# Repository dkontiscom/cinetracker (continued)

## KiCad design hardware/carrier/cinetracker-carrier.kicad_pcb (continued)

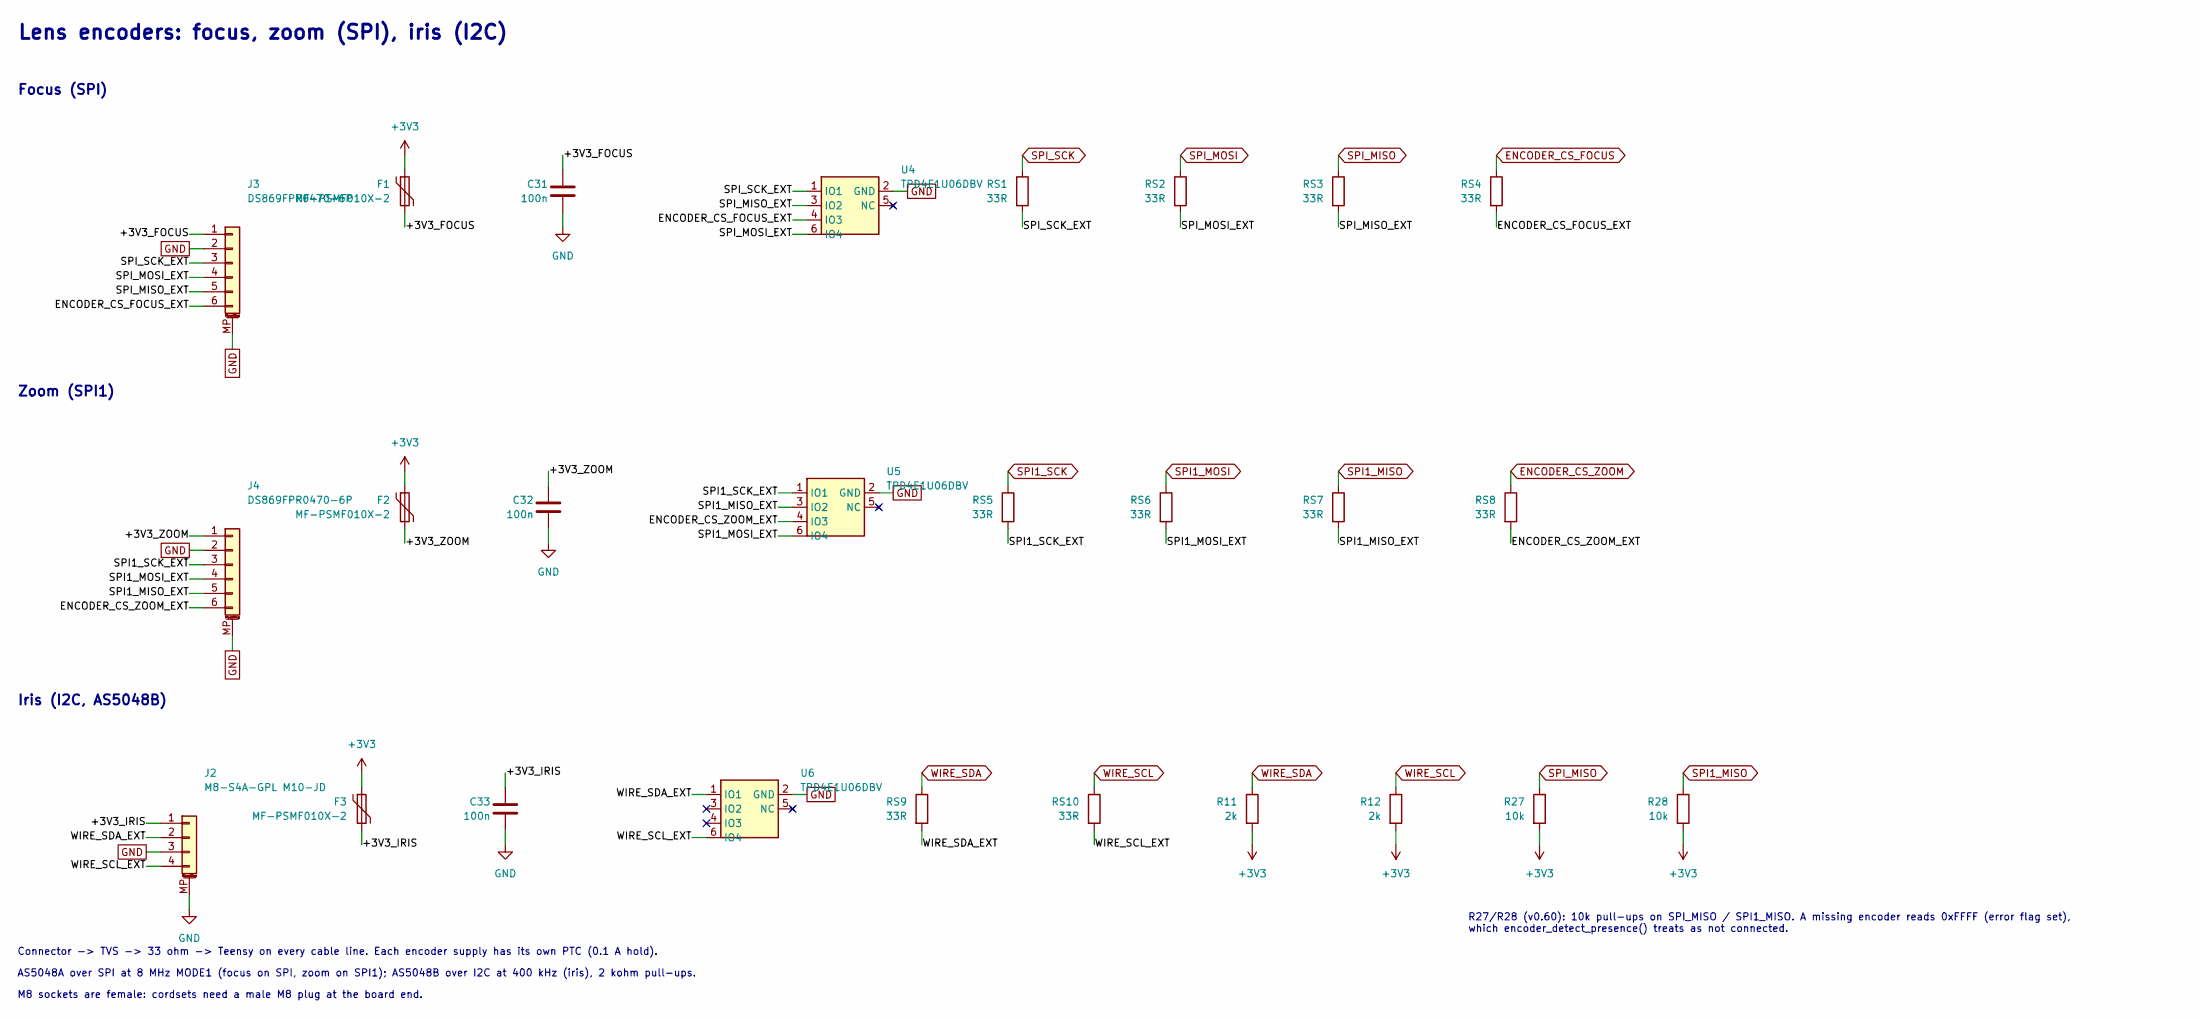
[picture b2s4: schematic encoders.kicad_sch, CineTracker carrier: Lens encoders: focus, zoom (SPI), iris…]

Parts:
C31, C32, C33: 100n; C_0805_2012Metric; MPN CC0805KRX7R9BB104; LCSC C49678
F1, F2, F3: MF-PSMF010X-2; Fuse_0805_2012Metric; MPN MF-PSMF010X-2; LCSC C116171
J2: M8-S4A-GPL M10-JD; M8_4pin_F_RA_CAZN; MPN M8-S4A-GPL M10-JD; LCSC C19108970
J3, J4: DS869FPR0470-6P; M8_6pin_F_RA_DOSIN; MPN DS869FPR0470-6P; LCSC C42395389
R11, R12: 2k; R_0805_2012Metric; MPN 0805W8F2001T5E; LCSC C17604
R27, R28: 10k; R_0805_2012Metric; MPN 0805W8F1002T5E; LCSC C17414
RS1, RS2, RS3, RS4, RS5, RS6, RS7, RS8, RS9, RS10: 33R; R_0805_2012Metric; MPN 0805W8F330JT5E; LCSC C17634
U4, U5, U6: TPD4E1U06DBV; SOT-23-6; MPN TPD4E1U06DBVR; LCSC C124691

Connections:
+3V3: F1.1, F2.1, F3.1, R11.2, R12.2, R27.2, R28.2; also elsewhere on the board
/Encoders/+3V3_FOCUS: C31.1, F1.2, J3.1
/Encoders/+3V3_IRIS: C33.1, F3.2, J2.1
/Encoders/+3V3_ZOOM: C32.1, F2.2, J4.1
/Encoders/ENCODER_CS_FOCUS_EXT: J3.6, RS4.2, U4.4 (IO3)
/Encoders/ENCODER_CS_ZOOM_EXT: J4.6, RS8.2, U5.4 (IO3)
/Encoders/SPI1_MISO_EXT: J4.5, RS7.2, U5.3 (IO2)
/Encoders/SPI1_MOSI_EXT: J4.4, RS6.2, U5.6 (IO4)
/Encoders/SPI1_SCK_EXT: J4.3, RS5.2, U5.1 (IO1)
/Encoders/SPI_MISO_EXT: J3.5, RS3.2, U4.3 (IO2)
/Encoders/SPI_MOSI_EXT: J3.4, RS2.2, U4.6 (IO4)
/Encoders/SPI_SCK_EXT: J3.3, RS1.2, U4.1 (IO1)
/Encoders/WIRE_SCL_EXT: J2.4, RS10.2, U6.6 (IO4)
/Encoders/WIRE_SDA_EXT: J2.2, RS9.2, U6.1 (IO1)
ENCODER_CS_FOCUS: RS4.1; also elsewhere on the board
ENCODER_CS_ZOOM: RS8.1; also elsewhere on the board
GND: C31.2, C32.2, C33.2, J2.3, J2.MP (MountPin), J3.2, J3.MP (MountPin), J4.2, J4.MP (MountPin), U4.2 (GND), U5.2 (GND), U6.2 (GND); also elsewhere on the board
SPI1_MISO: R28.1, RS7.1; also elsewhere on the board
SPI1_MOSI: RS6.1; also elsewhere on the board
SPI1_SCK: RS5.1; also elsewhere on the board
SPI_MISO: R27.1, RS3.1; also elsewhere on the board
SPI_MOSI: RS2.1; also elsewhere on the board
SPI_SCK: RS1.1; also elsewhere on the board
WIRE_SCL: R12.1, RS10.1; also elsewhere on the board
WIRE_SDA: R11.1, RS9.1; also elsewhere on the board

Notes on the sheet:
Lens encoders: focus, zoom (SPI), iris (I2C)
M8 sockets are female: cordsets need a male M8 plug at the board end.
Focus (SPI)
R27/R28 (v0.60): 10k pull-ups on SPI_MISO / SPI1_MISO. A missing encoder reads 0xFFFF (error flag set), which encoder_detect_presence() treats as not connected.
Iris (I2C, AS5048B)
AS5048A over SPI at 8 MHz MODE1 (focus on SPI, zoom on SPI1); AS5048B over I2C at 400 kHz (iris), 2 kohm pull-ups.
Zoom (SPI1)
Connector -> TVS -> 33 ohm -> Teensy on every cable line. Each encoder supply has its own PTC (0.1 A hold).

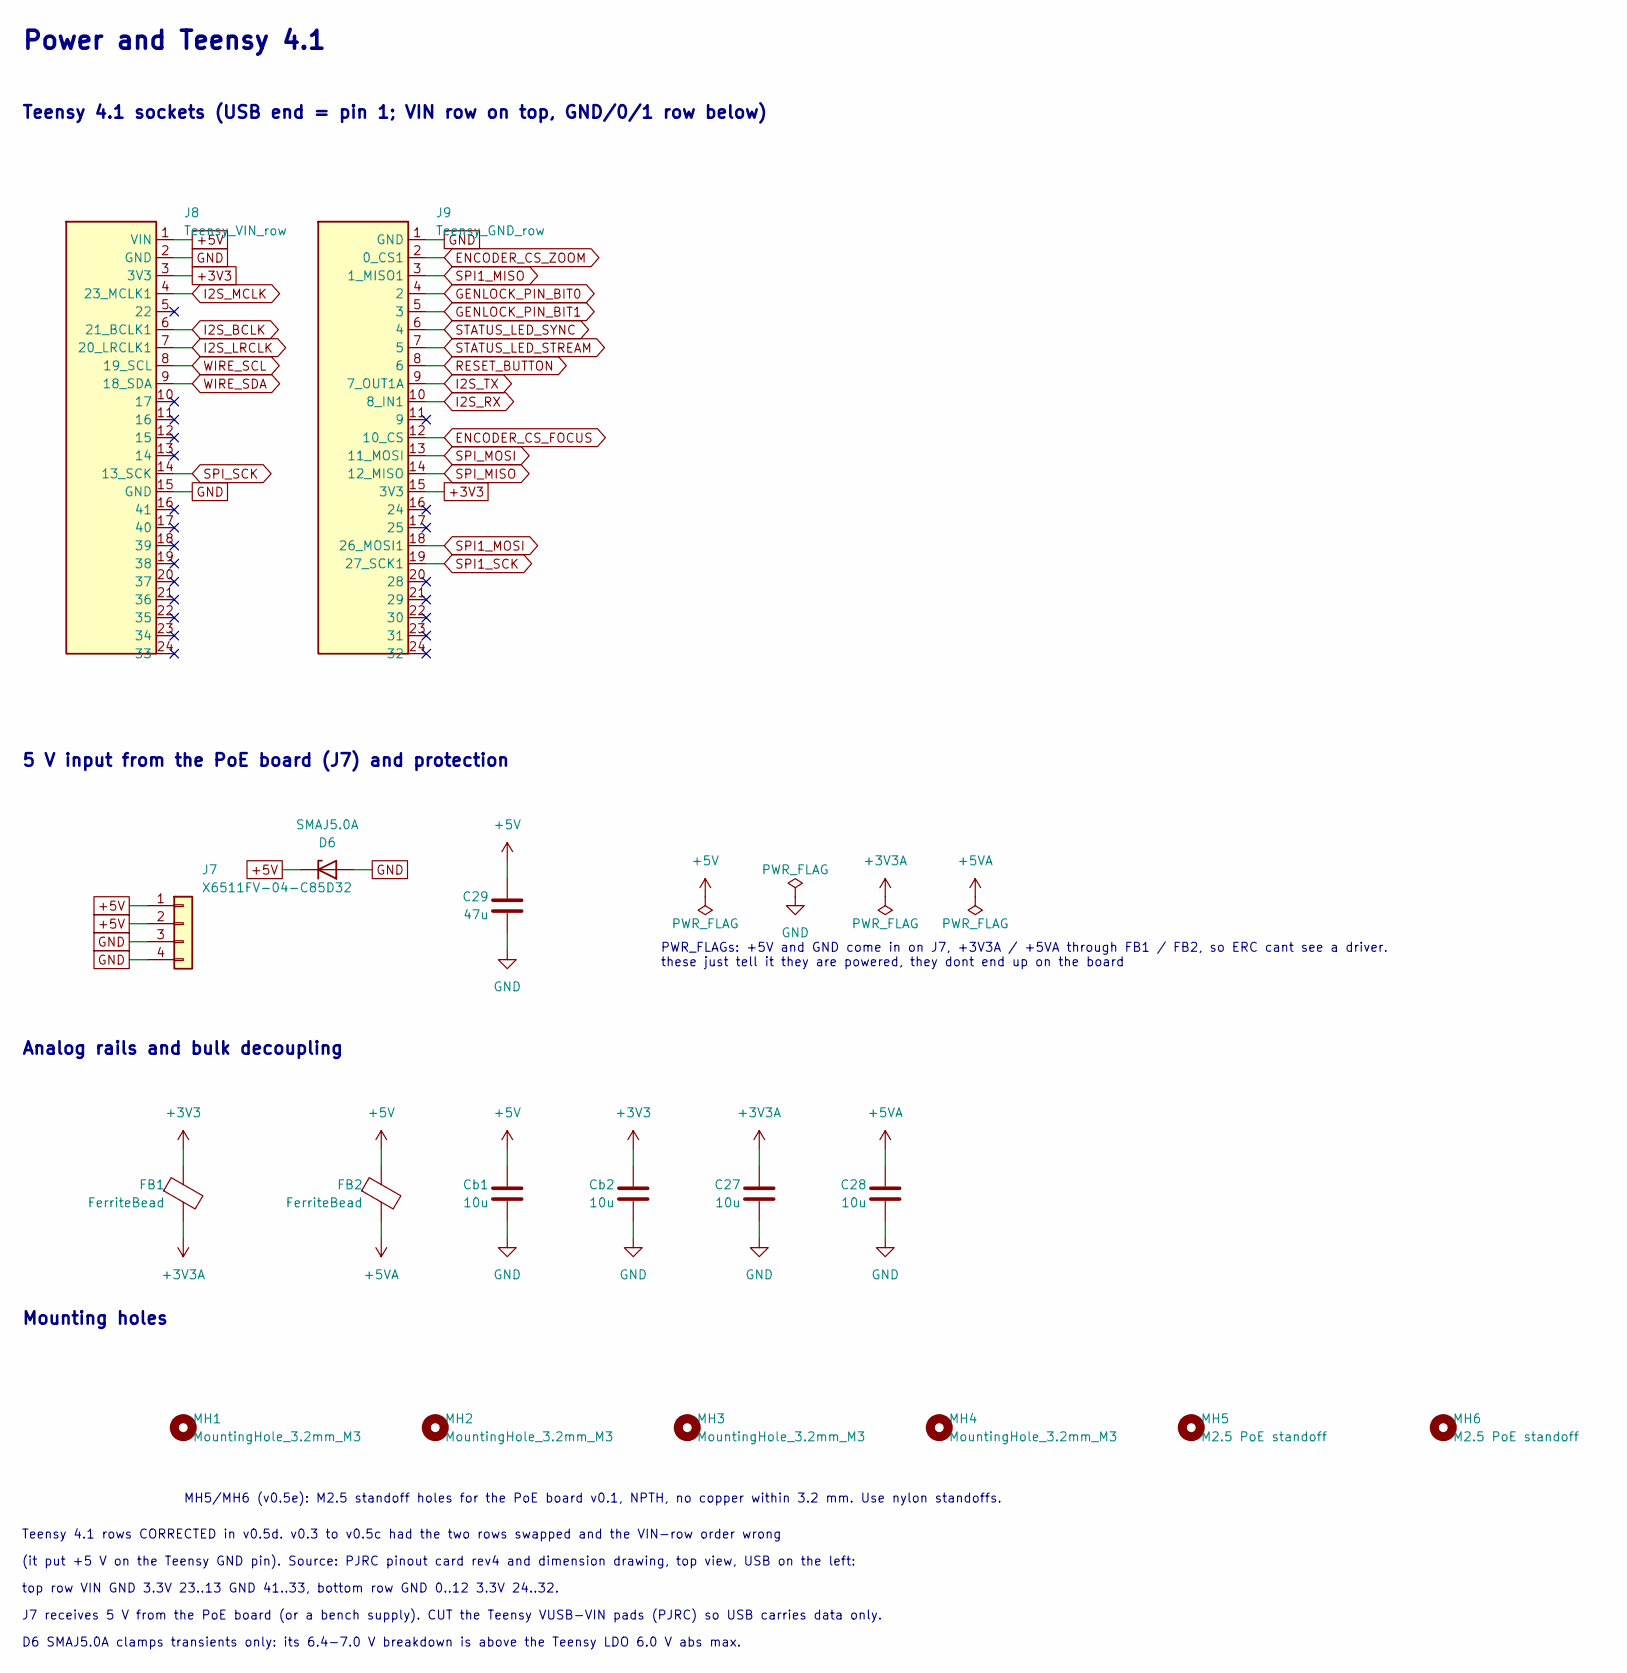
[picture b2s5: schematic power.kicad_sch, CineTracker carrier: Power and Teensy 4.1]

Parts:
C27, C28: 10u; C_0805_2012Metric; MPN CL21A106KAYNNNE; LCSC C15850
C29: 47u; C_1206_3216Metric; MPN CL31A476MPHNNNE; LCSC C96123
Cb1, Cb2: 10u; C_0805_2012Metric; MPN CL21A106KAYNNNE; LCSC C15850
D6: SMAJ5.0A; D_SMA; MPN SMAJ5.0A; LCSC C83329
FB1, FB2: FerriteBead; L_0805_2012Metric; MPN GZ2012D601TF; LCSC C1017
J7: X6511FV-04-C85D32; PinSocket_1x04_P2.54mm_Vertical; MPN X6511FV-04-C85D32; LCSC C718241
J8: Teensy_VIN_row; PinSocket_1x24_P2.54mm_Vertical; MPN X6511FV-24-C85D32; LCSC C2883741
J9: Teensy_GND_row; PinSocket_1x24_P2.54mm_Vertical; MPN X6511FV-24-C85D32; LCSC C2883741
MH1, MH2, MH3, MH4: MountingHole_3.2mm_M3
MH5, MH6: M2.5 PoE standoff; MountingHole_2.7mm_M2.5

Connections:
+3V3: Cb2.1, FB1.1, J8.3 (3V3), J9.15 (3V3); also elsewhere on the board
+3V3A: C27.1, FB1.2; also elsewhere on the board
+5V: C29.1, Cb1.1, D6.1 (K), FB2.1, J7.1, J7.2, J8.1 (VIN)
+5VA: C28.1, FB2.2; also elsewhere on the board
ENCODER_CS_FOCUS: J9.12 (10_CS); also elsewhere on the board
ENCODER_CS_ZOOM: J9.2 (0_CS1); also elsewhere on the board
GENLOCK_PIN_BIT0: J9.4 (2); also elsewhere on the board
GENLOCK_PIN_BIT1: J9.5 (3); also elsewhere on the board
GND: C27.2, C28.2, C29.2, Cb1.2, Cb2.2, D6.2 (A), J7.3, J7.4, J8.2 (GND), J8.15 (GND), J9.1 (GND); also elsewhere on the board
I2S_BCLK: J8.6 (21_BCLK1); also elsewhere on the board
I2S_LRCLK: J8.7 (20_LRCLK1); also elsewhere on the board
I2S_MCLK: J8.4 (23_MCLK1); also elsewhere on the board
I2S_RX: J9.10 (8_IN1); also elsewhere on the board
I2S_TX: J9.9 (7_OUT1A); also elsewhere on the board
RESET_BUTTON: J9.8 (6); also elsewhere on the board
SPI1_MISO: J9.3 (1_MISO1); also elsewhere on the board
SPI1_MOSI: J9.18 (26_MOSI1); also elsewhere on the board
SPI1_SCK: J9.19 (27_SCK1); also elsewhere on the board
SPI_MISO: J9.14 (12_MISO); also elsewhere on the board
SPI_MOSI: J9.13 (11_MOSI); also elsewhere on the board
SPI_SCK: J8.14 (13_SCK); also elsewhere on the board
STATUS_LED_STREAM: J9.7 (5); also elsewhere on the board
STATUS_LED_SYNC: J9.6 (4); also elsewhere on the board
WIRE_SCL: J8.8 (19_SCL); also elsewhere on the board
WIRE_SDA: J8.9 (18_SDA); also elsewhere on the board

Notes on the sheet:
Teensy 4.1 rows CORRECTED in v0.5d. v0.3 to v0.5c had the two rows swapped and the VIN-row order wrong
(it put +5 V on the Teensy GND pin). Source: PJRC pinout card rev4 and dimension drawing, top view, USB on the left:
Power and Teensy 4.1
J7 receives 5 V from the PoE board (or a bench supply). CUT the Teensy VUSB-VIN pads (PJRC) so USB carries data only.
Teensy 4.1 sockets (USB end = pin 1; VIN row on top, GND/0/1 row below)
Analog rails and bulk decoupling
top row VIN GND 3.3V 23..13 GND 41..33, bottom row GND 0..12 3.3V 24..32.
MH5/MH6 (v0.5e): M2.5 standoff holes for the PoE board v0.1, NPTH, no copper within 3.2 mm. Use nylon standoffs.
5 V input from the PoE board (J7) and protection
Mounting holes
D6 SMAJ5.0A clamps transients only: its 6.4-7.0 V breakdown is above the Teensy LDO 6.0 V abs max.
PWR_FLAGs: +5V and GND come in on J7, +3V3A / +5VA through FB1 / FB2, so ERC cant see a driver. these just tell it they are powered, they dont end up on the board

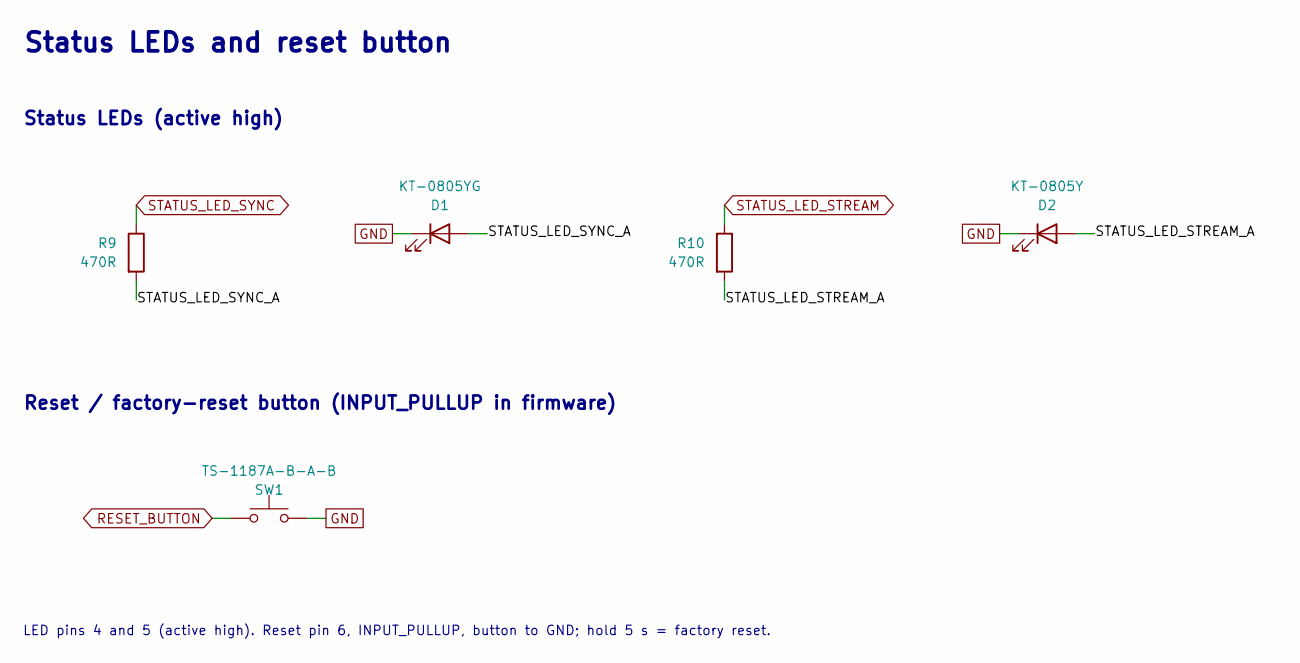
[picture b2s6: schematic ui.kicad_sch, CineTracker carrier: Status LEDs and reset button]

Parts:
D1: KT-0805YG; LED_0805_2012Metric; MPN KT-0805YG; LCSC C2292
D2: KT-0805Y; LED_0805_2012Metric; MPN KT-0805Y; LCSC C2296
R9, R10: 470R; R_0805_2012Metric; MPN 0805W8F4700T5E; LCSC C17710
SW1: TS-1187A-B-A-B; SW_Push_1P1T_XKB_TS-1187A; MPN TS-1187A-B-A-B; LCSC C318884

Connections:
/UI/STATUS_LED_STREAM_A: D2.2 (A), R10.2
/UI/STATUS_LED_SYNC_A: D1.2 (A), R9.2
GND: D1.1 (K), D2.1 (K), SW1.2; also elsewhere on the board
RESET_BUTTON: SW1.1; also elsewhere on the board
STATUS_LED_STREAM: R10.1; also elsewhere on the board
STATUS_LED_SYNC: R9.1; also elsewhere on the board

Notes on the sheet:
Reset / factory-reset button (INPUT_PULLUP in firmware)
Status LEDs and reset button
Status LEDs (active high)
LED pins 4 and 5 (active high). Reset pin 6, INPUT_PULLUP, button to GND; hold 5 s = factory reset.

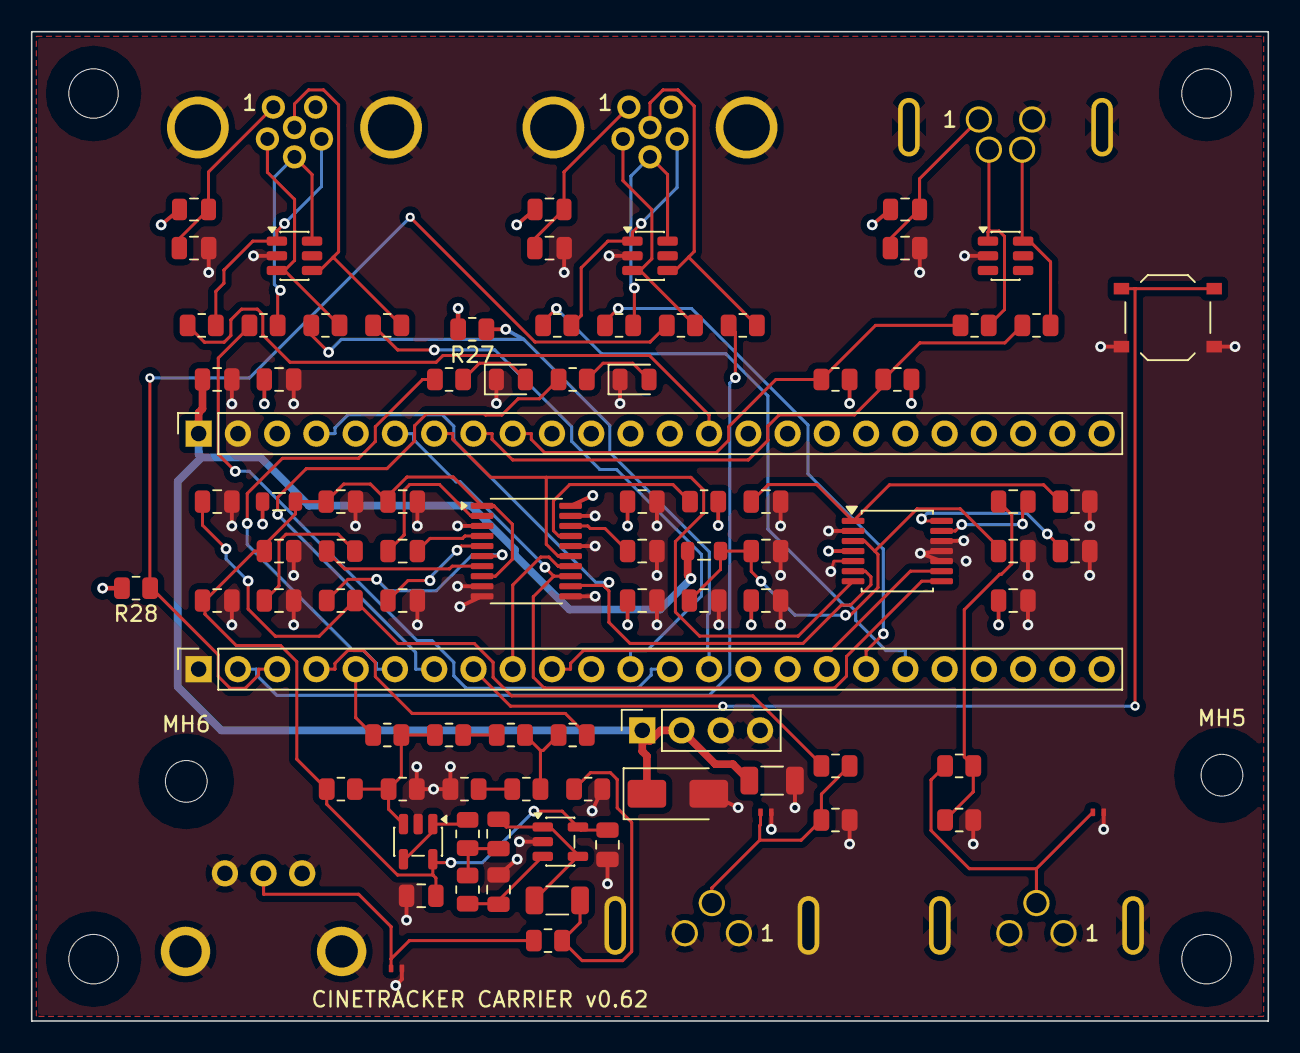
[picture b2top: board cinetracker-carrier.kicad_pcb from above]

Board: 4 copper layers, 80.0 x 64.0 mm, 100 parts (0 on the bottom side), 65 nets.

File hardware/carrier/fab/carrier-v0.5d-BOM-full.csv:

Qty/board,Designator,Description,Manufacturer,MPN,LCSC,JLC library,Process,JLC stock (2026-10-09),Bought for 5 boards (incl. attrition),Unit USD,Line USD
2,"C1,C29",47uF 10V X5R 1206,Samsung,CL31A476MPHNNNE,C96123,Basic,SMT,390311,14,0.2593,3.63
2,"C10,C11",2.2uF 25V X7R 0805,Samsung,CL21B225KAFNNNE,C19110,Extended,SMT,95214,20,0.0328,0.66
12,"C2,C12,C14,C15,C17,C20,C22,C24,C31,C32,C33,C34",100nF 50V X7R 0805,YAGEO,CC0805KRX7R9BB104,C49678,Basic,SMT,19830554,70,0.0189,1.32
9,"C13,C16,C21,C23,C25,C27,C28,Cb1,Cb2",10uF 25V X5R 0805,Samsung,CL21A106KAYNNNE,C15850,Basic,SMT,4326093,55,0.0688,3.78
2,"C18,C19",2.2nF 50V C0G 0805,Samsung,CL21C222JBFNNNE,C28260,Basic,SMT,100767,14,0.0202,0.28
2,"C26,C30",1uF 50V X7R 0805,Samsung,CL21B105KBFNNNE,C28323,Basic,SMT,1830276,20,0.04,0.8
2,"CF1,CF2",68pF 50V NP0/C0G ±1% 0805,YAGEO,CC0805FRNPO9BN680,C541517,Extended,SMT,6909,18,0.0334,0.6
1,D1,LED yellow-green 0805,Hubei KENTO,KT-0805YG,C2292,Extended,SMT,13261,15,0.0161,0.24
1,D2,LED yellow 0805,Hubei KENTO,KT-0805Y,C2296,Basic,SMT,322747,15,0.0153,0.23
3,"D3,D4,D5",bidir ESD +/-9V X1SON-2 (DPY),Texas Instruments,TPD1E10B09DPYR,C88031,Extended,SMT,120763,19,0.0891,1.69
1,D6,TVS 5V uni 400W SMA,Littelfuse,SMAJ5.0A,C83329,Extended,SMT,29987,7,0.1237,0.87
3,"F1,F2,F3",PTC 0.1A hold 0.3A trip 0805,Bourns,MF-PSMF010X-2,C116171,Extended,SMT,52217,23,0.0514,1.18
2,"FB1,FB2",600R@100MHz 500mA 0805,Sunlord,GZ2012D601TF,C1017,Basic,SMT,311721,20,0.0201,0.4
1,J1,BNC 75ohm RA bulkhead THT,Kinghelm,KH-BNC75-3511,C2837588,Extended,THT (hand/wave),738,5,0.9496,4.75
1,J2,M8 4P A female RA THT,CAZN,M8-S4A-GPL M10-JD,C19108970,Extended,THT (hand/wave),264,5,5.0197,25.1
2,"J3,J4",M8 6P A female RA THT,dosinconn,DS869FPR0470-6P,C42395389,Extended,THT (hand/wave),53,10,3.8584,38.58
2,"J5,J6",M8 3P female RA THT,CAZN,M8-S3A-GPLM10,C42931206,Extended,THT (hand/wave),265,10,4.1157,41.16
1,J7,1x4 female 2.54mm 8.5mm THT (5V in),XKB Connection,X6511FV-04-C85D32,C718241,Extended,THT (hand/wave),5001,6,0.2053,1.23
2,"J8,J9",1x24 female 2.54mm 8.5mm THT,XKB Connection,X6511FV-24-C85D32,C2883741,Extended,THT (hand/wave),978,10,0.645,6.45
5,"R1,R2,R4,R11,R12",2k 1% 0805,UNI-ROYAL,0805W8F2001T5E,C17604,Basic,SMT,5276932,35,0.0039,0.14
4,"R9,R10,R21,R22",470R 1% 0805,UNI-ROYAL,0805W8F4700T5E,C17710,Basic,SMT,2705681,30,0.0048,0.14
1,R13,11R 1% 0805,UNI-ROYAL,0805W8F110JT5E,C17430,Extended,SMT,19227,15,0.0042,0.06
1,R14,22R 1% 0805,UNI-ROYAL,0805W8F220JT5E,C17561,Basic,SMT,1632246,15,0.0045,0.07
1,R15,5.6k 1% 0805,UNI-ROYAL,0805W8F5601T5E,C4382,Basic,SMT,592554,15,0.0062,0.09
3,"R7,R20,R25",10k 1% 0805,UNI-ROYAL,0805W8F1002T5E,C17414,Basic,SMT,58515108,25,0.0033,0.08
1,R23,4.7k 1% 0805,UNI-ROYAL,0805W8F4701T5E,C17673,Basic,SMT,4704124,11,0.005,0.06
1,R24,20k 1% 0805,UNI-ROYAL,0805W8F2002T5E,C4328,Basic,SMT,2351214,15,0.0042,0.06
2,"R3,R26",1k 1% 0805,UNI-ROYAL,0805W8F1001T5E,C17513,Basic,SMT,45449859,20,0.0035,0.07
1,R5,5.1k 1% 0805,UNI-ROYAL,0805W8F5101T5E,C27834,Basic,SMT,3080531,15,0.0056,0.08
1,R6,75R 1% 0805,YAGEO,RC0805FR-0775RL,C141697,Extended,SMT,145170,15,0.0076,0.11
2,"RF1,RF2",150R 1% 0805,UNI-ROYAL,0805W8F1500T5E,C17471,Basic,SMT,441252,20,0.0056,0.11
10,"RS1,RS2,RS3,RS4,RS5,RS6,RS7,RS8,RS9,RS10",33R 1% 0805,UNI-ROYAL,0805W8F330JT5E,C17634,Basic,SMT,1515996,60,0.0047,0.28
1,SW1,Tact switch 5.1x5.1 SMD,XKB Connection,TS-1187A-B-A-B,C318884,Basic,SMT,382168,10,0.0206,0.21
2,"U1,U7",200MHz 360V/us op-amp SOT-23-5,Texas Instruments,OPA356AIDBVR,C183100,Extended,SMT,947,10,1.0294,10.29
1,U2,Audio ADC 24-bit I2S TSSOP-14,Texas Instruments,PCM1808PWR,C55513,Extended,SMT,15563,5,0.702,3.51
1,U3,Audio DAC 32-bit I2S TSSOP-20,Texas Instruments,PCM5102APWR,C107671,Extended,SMT,7771,5,1.4463,7.23
3,"U4,U5,U6",4-ch ESD 5.5V SOT-23-6,Texas Instruments,TPD4E1U06DBVR,C124691,Extended,SMT,23216,15,0.3649,5.47

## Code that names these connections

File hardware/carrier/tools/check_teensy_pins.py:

# SPDX-FileCopyrightText: 2026 Dimitris Kontis and CineTracker contributors
# SPDX-License-Identifier: CERN-OHL-S-2.0
"""Independent check: Teensy 4.1 pins on the carrier vs PJRC card + firmware.
usage: python3 check_teensy_pins.py ../cinetracker-carrier.kicad_pcb   (needs KiCad 10's pcbnew python module)
J8 = VIN-row socket, J9 = GND/0/1-row socket.
Source of the pin order: PJRC pinout card card11a_rev4 (top view, USB on the left):
top row VIN GND 3.3V 23..13 GND 41..33, bottom row GND 0..12 3.3V 24..32."""
import pcbnew, sys
B=sys.argv[1]
TOP=["VIN","GND","3V3"]+[str(n) for n in range(23,12,-1)]+["GND"]+[str(n) for n in range(41,32,-1)]
BOT=["GND"]+[str(n) for n in range(0,13)]+["3V3"]+[str(n) for n in range(24,33)]
assert len(TOP)==24 and len(BOT)==24
FW={"VIN":"+5V","3V3":"+3V3","GND":"GND",
    "2":"GENLOCK_PIN_BIT0","3":"GENLOCK_PIN_BIT1",           # include/genlock.h
    "4":"STATUS_LED_SYNC","5":"STATUS_LED_STREAM",          # include/status_leds.h
    "6":"RESET_BUTTON",                                      # include/reset_button.h
    "10":"ENCODER_CS_FOCUS","0":"ENCODER_CS_ZOOM",           # include/encoder_driver.h
    "11":"SPI_MOSI","12":"SPI_MISO","13":"SPI_SCK",          # SPI default pins
    "26":"SPI1_MOSI","1":"SPI1_MISO","27":"SPI1_SCK",        # SPI1 default pins (core SPI.cpp lpspi3: MISO 1, MOSI 26, SCK 27)
    "18":"WIRE_SDA","19":"WIRE_SCL",                         # Wire default pins
    "7":"I2S_TX","8":"I2S_RX","23":"I2S_MCLK","21":"I2S_BCLK","20":"I2S_LRCLK"}  # SAI1 (OUT1A, IN1, MCLK1, BCLK1, LRCLK1)
b=pcbnew.LoadBoard(B); bad=0
pads=[p for f in b.GetFootprints() if f.GetReference() in ("J8","J9") for p in f.Pads()]
ys=sorted({round(pcbnew.ToMM(p.GetPosition().y),2) for p in pads}); assert len(ys)==2, ys
top_y,bot_y=ys
x0=min(pcbnew.ToMM(p.GetPosition().x) for p in pads)
for p in pads:
    x=pcbnew.ToMM(p.GetPosition().x); y=round(pcbnew.ToMM(p.GetPosition().y),2)
    i=round((x-x0)/2.54); name=(TOP if y==top_y else BOT)[i]
    want=FW.get(name,"")
    got=p.GetNetname()
    if got.startswith("unconnected-"): got=""   # no-connect pin, KiCad 10 gives it its own unconnected-... net
    if got!=want:
        bad+=1; print(f"MISMATCH {p.GetParent().GetReference()}.{p.GetNumber()} Teensy {name}: board '{got}' expected '{want}'")
# USB end must be the low-x end and the USB end must be where VIN/GND sit
print("rows y:",ys,"USB end x:",round(x0,2),"| mismatches:",bad)
sys.exit(1 if bad else 0)
